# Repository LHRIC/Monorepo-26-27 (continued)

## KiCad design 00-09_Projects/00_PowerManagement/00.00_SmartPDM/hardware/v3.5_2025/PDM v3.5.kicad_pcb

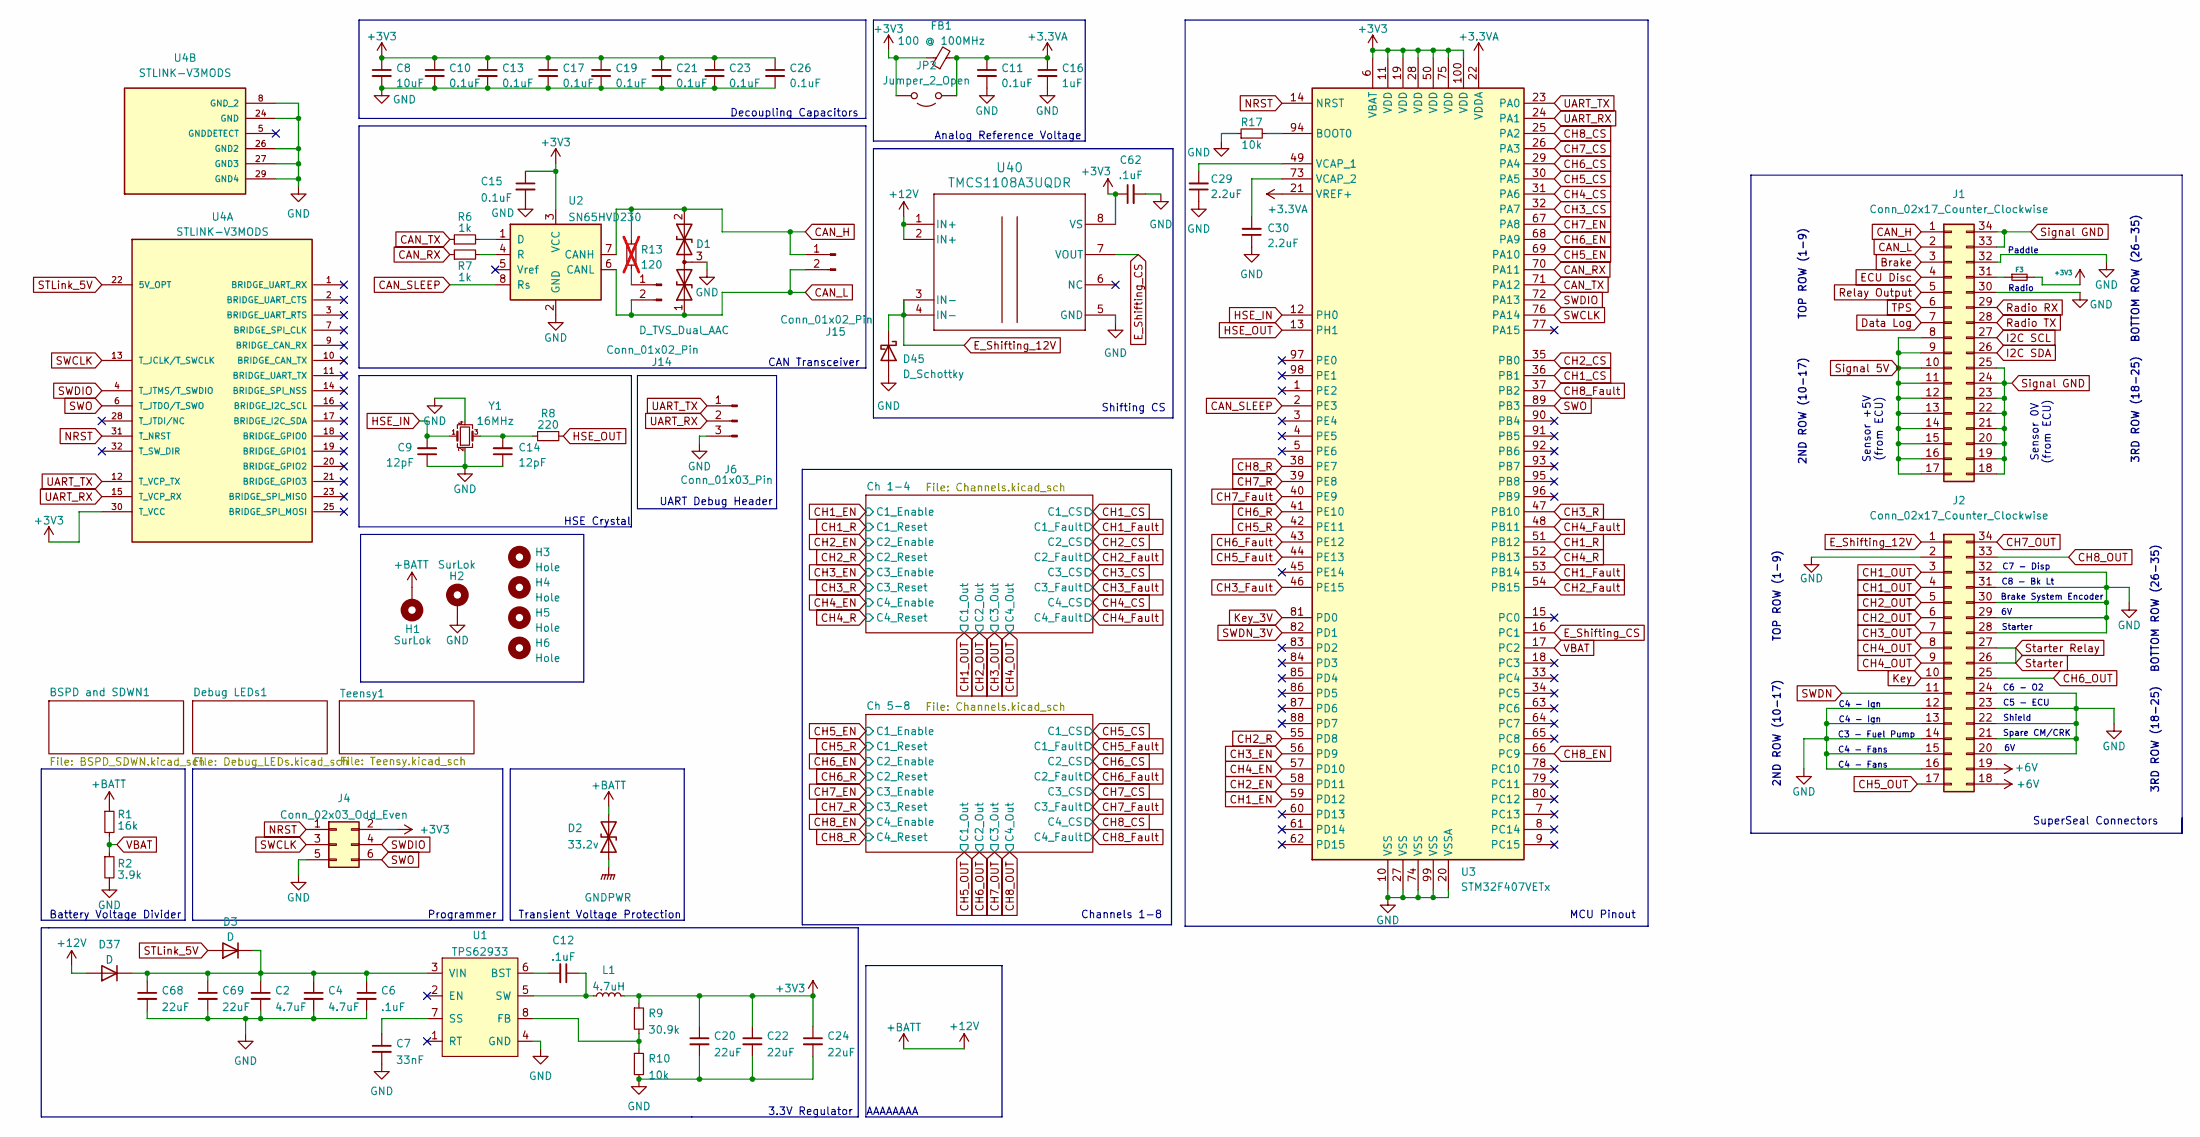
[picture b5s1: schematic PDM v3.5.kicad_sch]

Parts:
C2, C4: 4.7uF; C_0805_2012Metric
C6, C12, C62: .1uF; C_0603_1608Metric
C7: 33nF; C_0603_1608Metric
C8: 10uF; C_0805_2012Metric
C9, C14: 12pF; C_0402_1005Metric
C10, C11, C13, C15, C17, C19, C21, C23, C26: 0.1uF; C_0603_1608Metric
C16: 1uF; C_0603_1608Metric
C20, C22, C24, C68, C69: 22uF; C_0805_2012Metric
C29, C30: 2.2uF; C_0603_1608Metric
D1: D_TVS_Dual_AAC; SOT-23
D2: 33.2v; D_SMB
D3, D37: D; D_PowerDI-123
D45: D_Schottky; D_SOD-523
F3: Fuse_1206_3216Metric; LCSC C70071
FB1: 100 @ 100MHz; C_0402_1005Metric
H1, H2: SurLok; SurLok_5.7
H3, H4, H5, H6: Hole; MountingHole_3.2mm_M3
J1: Conn_02x17_Counter_Clockwise; TE_6437288-1
J2: Conn_02x17_Counter_Clockwise; TE_6437288-2
J4: Conn_02x03_Odd_Even; Molex_Micro-Fit_3.0_43045-0612_2x03_P3.00mm_Vertical
J6: Conn_01x03_Pin; PinHeader_1x03_P2.54mm_Vertical
J14, J15: Conn_01x02_Pin; PinHeader_1x02_P2.54mm_Vertical
JP2: Jumper_2_Open; SolderJumper-2_P1.3mm_Open_RoundedPad1.0x1.5mm
L1: 4.7uH; SRU8043-4R7Y
R1: 16k; R_0603_1608Metric
R2: 3.9k; R_0603_1608Metric
R6, R7: 1k; R_0603_1608Metric
R8: 220; R_0603_1608Metric
R9: 30.9k; R_0603_1608Metric
R10, R17: 10k; R_0603_1608Metric
R13: 120; R_0603_1608Metric; not fitted
U1: TPS62933; SOT-583
U2: SN65HVD230; SOIC-8_3.9x4.9mm_P1.27mm
U3: STM32F407VETx; LQFP-100_14x14mm_P0.5mm
U4: STLINK-V3MODS; MODULE_STLINK-V3MODS; PARTREV 1; DigiKey_Part_Number 497-STLINK-V3MODS-ND
U40: TMCS1108A3UQDR; SOIC-8_3.9x4.9mm_P1.27mm
Y1: 16MHz; Crystal_SMD_3225-4Pin_3.2x2.5mm

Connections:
+3.3VA: C11.1, C16.1, FB1.2, JP2.1 (A), U3.21 (VREF+), U3.22 (VDDA)
+3V3: C8.1, C10.1, C13.1, C15.1, C17.1, C19.1, C20.1, C21.1, C22.1, C23.1, C24.1, C26.1, C62.1, F3.2, FB1.1, J4.2, JP2.2 (B), L1.2, R9.1, U2.3 (VCC), U3.6 (VBAT), U3.11 (VDD), U3.19 (VDD), U3.28 (VDD), U3.50 (VDD), U3.75 (VDD), U3.100 (VDD), U4.30 (T_VCC), U40.8 (VS); also elsewhere on the board
+6V: J2.18, J2.19; also elsewhere on the board
+12V: D2.2 (A2), D37.2 (A), H1.1, R1.1, U40.1 (IN+), U40.2 (IN+); also elsewhere on the board
Brake: J1.3; also elsewhere on the board
CAN_H: D1.2 (A2), J1.1, J15.1, R13.1, U2.7 (CANH); also elsewhere on the board
CAN_L: D1.1 (A1), J1.2, J14.2, J15.2, U2.6 (CANL); also elsewhere on the board
CAN_RX: R7.1, U3.70 (PA11)
CAN_SLEEP: U2.8 (Rs), U3.2 (PE3)
CAN_TX: R6.1, U3.71 (PA12)
CH1_CS: U3.36 (PB1); also elsewhere on the board
CH1_EN: U3.59 (PD12); also elsewhere on the board
CH1_Fault: U3.53 (PB14); also elsewhere on the board
CH1_OUT: J2.3, J2.4; also elsewhere on the board
CH1_R: U3.51 (PB12); also elsewhere on the board
CH2_CS: U3.35 (PB0); also elsewhere on the board
CH2_EN: U3.58 (PD11); also elsewhere on the board
CH2_Fault: U3.54 (PB15); also elsewhere on the board
CH2_OUT: J2.5, J2.6; also elsewhere on the board
CH2_R: U3.55 (PD8); also elsewhere on the board
CH3_CS: U3.32 (PA7); also elsewhere on the board
CH3_EN: U3.56 (PD9); also elsewhere on the board
CH3_Fault: U3.46 (PE15); also elsewhere on the board
CH3_OUT: J2.7; also elsewhere on the board
CH3_R: U3.47 (PB10); also elsewhere on the board
CH4_CS: U3.31 (PA6); also elsewhere on the board
CH4_EN: U3.57 (PD10); also elsewhere on the board
CH4_Fault: U3.48 (PB11); also elsewhere on the board
CH4_OUT: J2.8, J2.9; also elsewhere on the board
CH4_R: U3.52 (PB13); also elsewhere on the board
CH5_CS: U3.30 (PA5); also elsewhere on the board
CH5_EN: U3.69 (PA10); also elsewhere on the board
CH5_Fault: U3.44 (PE13); also elsewhere on the board
CH5_OUT: J2.17; also elsewhere on the board
CH5_R: U3.42 (PE11); also elsewhere on the board
CH6_CS: U3.29 (PA4); also elsewhere on the board
CH6_EN: U3.68 (PA9); also elsewhere on the board
CH6_Fault: U3.43 (PE12); also elsewhere on the board
CH6_OUT: J2.25; also elsewhere on the board
CH6_R: U3.41 (PE10); also elsewhere on the board
CH7_CS: U3.26 (PA3); also elsewhere on the board
CH7_EN: U3.67 (PA8); also elsewhere on the board
CH7_Fault: U3.40 (PE9); also elsewhere on the board
CH7_OUT: J2.34; also elsewhere on the board
CH7_R: U3.39 (PE8); also elsewhere on the board
CH8_CS: U3.25 (PA2); also elsewhere on the board
CH8_EN: U3.66 (PC9); also elsewhere on the board
CH8_Fault: U3.37 (PB2); also elsewhere on the board
CH8_OUT: J2.33; also elsewhere on the board
CH8_R: U3.38 (PE7); also elsewhere on the board
Data Log: J1.7; also elsewhere on the board
ECU Disc: J1.4; also elsewhere on the board
E_Shifting_12V: D45.1 (K), J2.1, U40.3 (IN-), U40.4 (IN-)
E_Shifting_CS: U3.16 (PC1), U40.7 (VOUT)
GND: C2.2, C4.2, C6.2, C7.2, C8.2, C9.1, C10.2, C11.2, C13.2, C14.1, C15.2, C16.2, C17.2, C19.2, C20.2, C21.2, C22.2, C23.2, C24.2, C26.2, C29.1, C30.1, C62.2, C68.2, C69.2, D1.3 (common), D45.2 (A), H2.1, J1.30, J1.32, J2.2, J2.12, J2.13, J2.14, J2.15, J2.16, J2.20, J2.21, J2.22, J2.23, J2.24, J2.28, J2.29, J2.30, J2.31, J2.32, J4.5, J6.3, R2.2, R10.2, R17.1, U1.4 (GND), U2.2 (GND), U3.10 (VSS), U3.20 (VSSA), U3.27 (VSS), U3.74 (VSS), U3.99 (VSS), U4.8 (GND_2), U4.24 (GND), U4.26 (GND2), U4.27 (GND3), U4.29 (GND4), U40.5 (GND), Y1.2, Y1.4; also elsewhere on the board
GNDPWR: D2.1 (A1)
HSE_IN: C9.2, U3.12 (PH0), Y1.1
HSE_OUT: R8.2, U3.13 (PH1)
I2C SCL: J1.27; also elsewhere on the board
I2C SDA: J1.26; also elsewhere on the board
Key: J2.10; also elsewhere on the board
Key_3V: U3.81 (PD0); also elsewhere on the board
NRST: J4.1, U3.14 (NRST), U4.31 (T_NRST)
unnamed: C14.2, R8.1, Y1.3
unnamed: C2.1, C4.1, C6.1, C68.1, C69.1, D3.1 (K), D37.1 (K), U1.3 (VIN)
unnamed: F3.1, J1.31
unnamed: J14.1, R13.2
unnamed: C12.2, U1.6 (BST)
unnamed: R9.2, R10.1, U1.8 (FB)
unnamed: C7.1, U1.7 (SS)
unnamed: C12.1, L1.1, U1.5 (SW)
unnamed: R6.2, U2.1 (D)
unnamed: R7.2, U2.4 (R)
unnamed: R17.2, U3.94 (BOOT0)
unnamed: C29.2, U3.49 (VCAP_1)
unnamed: C30.2, U3.73 (VCAP_2)
Radio RX: J1.29; also elsewhere on the board
Radio TX: J1.28; also elsewhere on the board
Relay Output: J1.5; also elsewhere on the board
STLink_5V: D3.2 (A), U4.22 (5V_OPT)
SWCLK: J4.3, U3.76 (PA14), U4.13 (T_JCLK/T_SWCLK)
SWDIO: J4.4, U3.72 (PA13), U4.4 (T_JTMS/T_SWDIO)
SWDN: J2.11; also elsewhere on the board
SWDN_3V: U3.82 (PD1); also elsewhere on the board
SWO: J4.6, U3.89 (PB3), U4.6 (T_JTDO/T_SWO)
Signal 5V: J1.8, J1.9, J1.10, J1.11, J1.12, J1.13, J1.14, J1.15, J1.16, J1.17
Signal GND: J1.18, J1.19, J1.20, J1.21, J1.22, J1.23, J1.24, J1.25, J1.33, J1.34
Starter: J2.26, J2.27
TPS: J1.6; also elsewhere on the board
UART_RX: J6.2, U3.24 (PA1), U4.15 (T_VCP_RX)
UART_TX: J6.1, U3.23 (PA0), U4.12 (T_VCP_TX)
VBAT: R1.2, R2.1, U3.17 (PC2)

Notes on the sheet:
C3 - Fuel Pump
Starter
TOP ROW (1-9)
Spare CM/CRK
3RD ROW (18-25)
Brake System Encoder
BOTTOM ROW (26-35)
MCU Pinout
UART Debug Header
2ND ROW (10-17)
C4 - Fans
Transient Voltage Protection
SuperSeal Connectors
HSE Crystal
Paddle
C5 - ECU
Radio
Shield
C6 - O2
3.3V Regulator
C4 - Ign
C7 - Disp
C8 - Bk Lt
Sensor +5V (from ECU)
Channels 1-8
Decoupling Capacitors
Battery Voltage Divider
CAN Transceiver
AAAAAAAA
Shifting CS
Programmer
Sensor 0V (from ECU)
Analog Reference Voltage

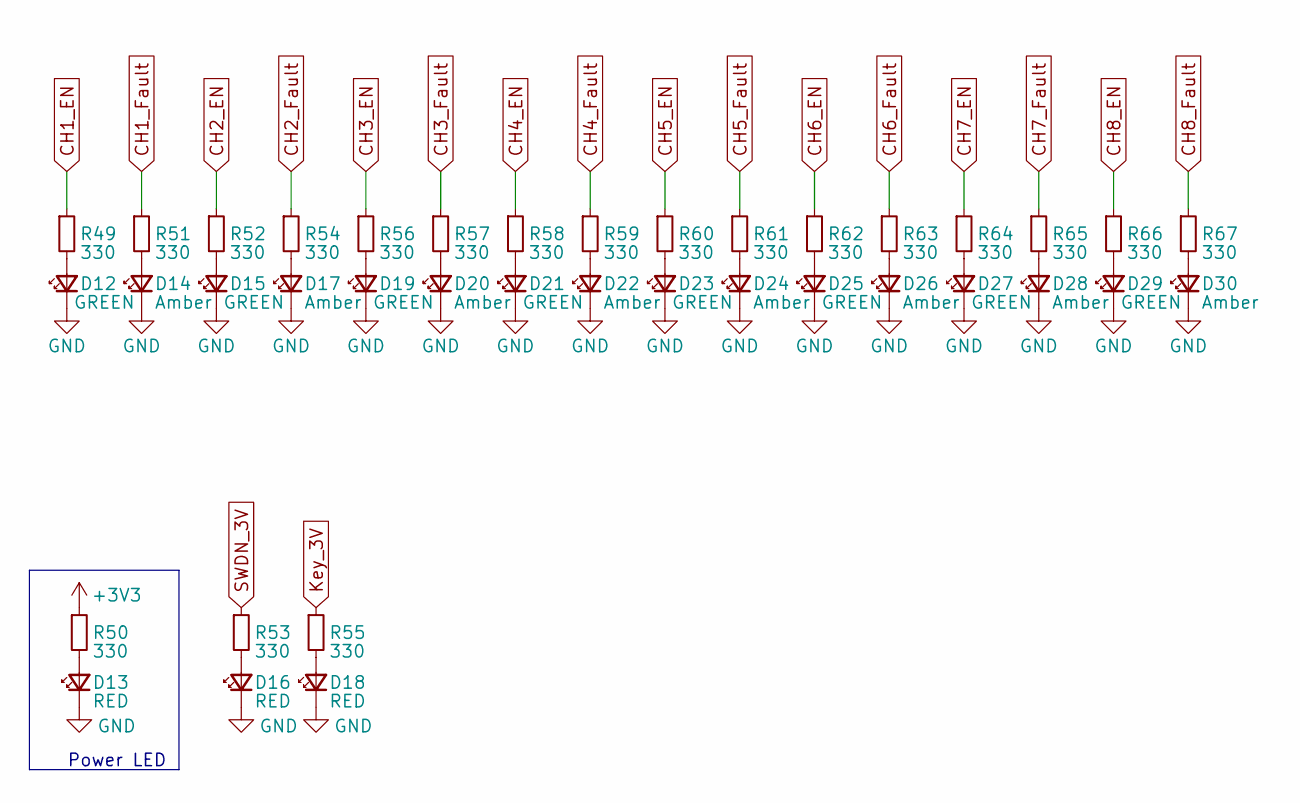
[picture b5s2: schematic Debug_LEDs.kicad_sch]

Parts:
D12, D15, D19, D21, D23, D25, D27, D29: GREEN; LED_0603_1608Metric
D13, D16, D18: RED; LED_0603_1608Metric
D14, D17, D20, D22, D24, D26, D28, D30: Amber; LED_0603_1608Metric
R49, R50, R51, R52, R53, R54, R55, R56, R57, R58, R59, R60, R61, R62, R63, R64, R65, R66, R67: 330; R_0603_1608Metric

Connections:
+3V3: R50.1; also elsewhere on the board
CH1_EN: R49.1; also elsewhere on the board
CH1_Fault: R51.1; also elsewhere on the board
CH2_EN: R52.1; also elsewhere on the board
CH2_Fault: R54.1; also elsewhere on the board
CH3_EN: R56.1; also elsewhere on the board
CH3_Fault: R57.1; also elsewhere on the board
CH4_EN: R58.1; also elsewhere on the board
CH4_Fault: R59.1; also elsewhere on the board
CH5_EN: R60.1; also elsewhere on the board
CH5_Fault: R61.1; also elsewhere on the board
CH6_EN: R62.1; also elsewhere on the board
CH6_Fault: R63.1; also elsewhere on the board
CH7_EN: R64.1; also elsewhere on the board
CH7_Fault: R65.1; also elsewhere on the board
CH8_EN: R66.1; also elsewhere on the board
CH8_Fault: R67.1; also elsewhere on the board
GND: D12.1 (K), D13.1 (K), D14.1 (K), D15.1 (K), D16.1 (K), D17.1 (K), D18.1 (K), D19.1 (K), D20.1 (K), D21.1 (K), D22.1 (K), D23.1 (K), D24.1 (K), D25.1 (K), D26.1 (K), D27.1 (K), D28.1 (K), D29.1 (K), D30.1 (K); also elsewhere on the board
Key_3V: R55.1; also elsewhere on the board
unnamed: D12.2 (A), R49.2
unnamed: D13.2 (A), R50.2
unnamed: D14.2 (A), R51.2
unnamed: D15.2 (A), R52.2
unnamed: D16.2 (A), R53.2
unnamed: D17.2 (A), R54.2
unnamed: D18.2 (A), R55.2
unnamed: D19.2 (A), R56.2
unnamed: D20.2 (A), R57.2
unnamed: D21.2 (A), R58.2
unnamed: D22.2 (A), R59.2
unnamed: D23.2 (A), R60.2
unnamed: D24.2 (A), R61.2
unnamed: D25.2 (A), R62.2
unnamed: D26.2 (A), R63.2
unnamed: D27.2 (A), R64.2
unnamed: D28.2 (A), R65.2
unnamed: D29.2 (A), R66.2
unnamed: D30.2 (A), R67.2
SWDN_3V: R53.1; also elsewhere on the board

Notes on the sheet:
Power LED

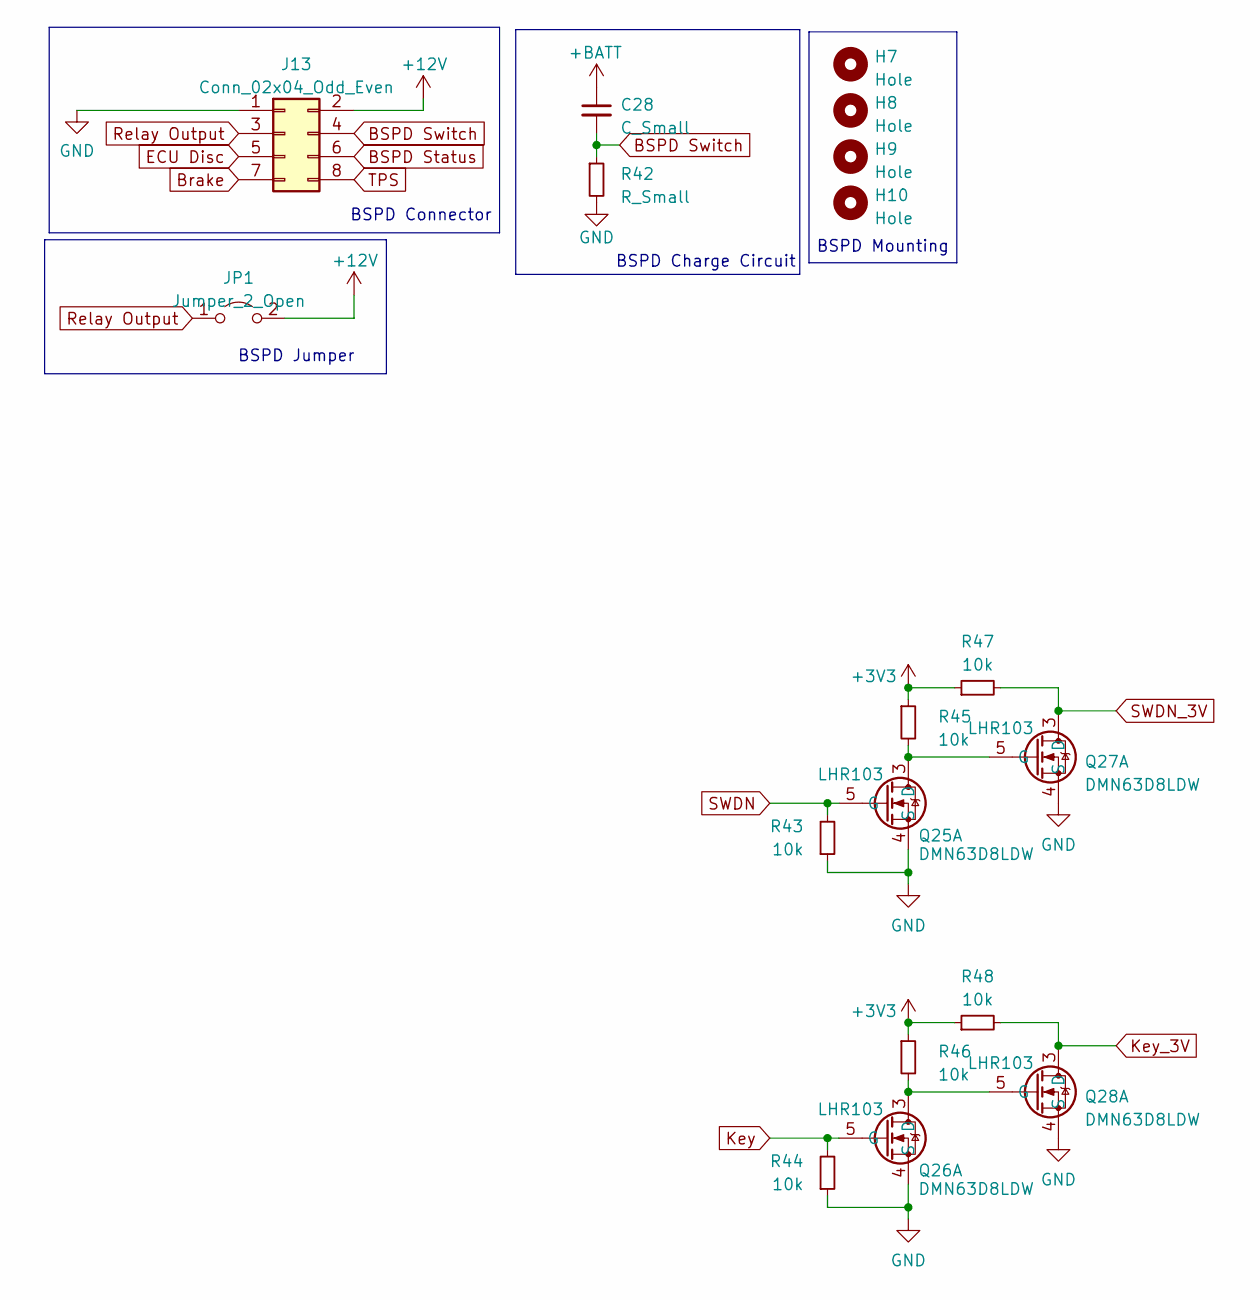
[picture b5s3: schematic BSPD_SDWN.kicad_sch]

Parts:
C28: C_Small; C_0805_2012Metric
H7, H8, H9, H10: Hole; MountingHole_3.7mm
J13: Conn_02x04_Odd_Even; SAMTEC-SFM-104-02-X-D-A
JP1: Jumper_2_Open; SolderJumper-2_P1.3mm_Open_RoundedPad1.0x1.5mm
Q25, Q26, Q27, Q28: DMN63D8LDW; SOT-363_SC-70-6
R42: R_Small; R_0603_1608Metric
R43, R44, R45, R46, R47, R48: 10k; R_0603_1608Metric

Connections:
+3V3: R45.1, R46.1, R47.1, R48.1; also elsewhere on the board
+12V: C28.1, J13.2, JP1.2 (B); also elsewhere on the board
BSPD Status: J13.6; also elsewhere on the board
BSPD Switch: C28.2, J13.4, R42.1
Brake: J13.7; also elsewhere on the board
ECU Disc: J13.5; also elsewhere on the board
GND: J13.1, Q25.4 (S), Q26.4 (S), Q27.4 (S), Q28.4 (S), R42.2, R43.1, R44.1; also elsewhere on the board
Key: Q26.5 (G), R44.2; also elsewhere on the board
Key_3V: Q28.3 (D), R48.2; also elsewhere on the board
unnamed: Q25.3 (D), Q27.5 (G), R45.2
unnamed: Q26.3 (D), Q28.5 (G), R46.2
Relay Output: J13.3, JP1.1 (A); also elsewhere on the board
SWDN: Q25.5 (G), R43.2; also elsewhere on the board
SWDN_3V: Q27.3 (D), R47.2; also elsewhere on the board
TPS: J13.8; also elsewhere on the board

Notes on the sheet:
BSPD Charge Circuit
BSPD Mounting
BSPD Connector
BSPD Jumper

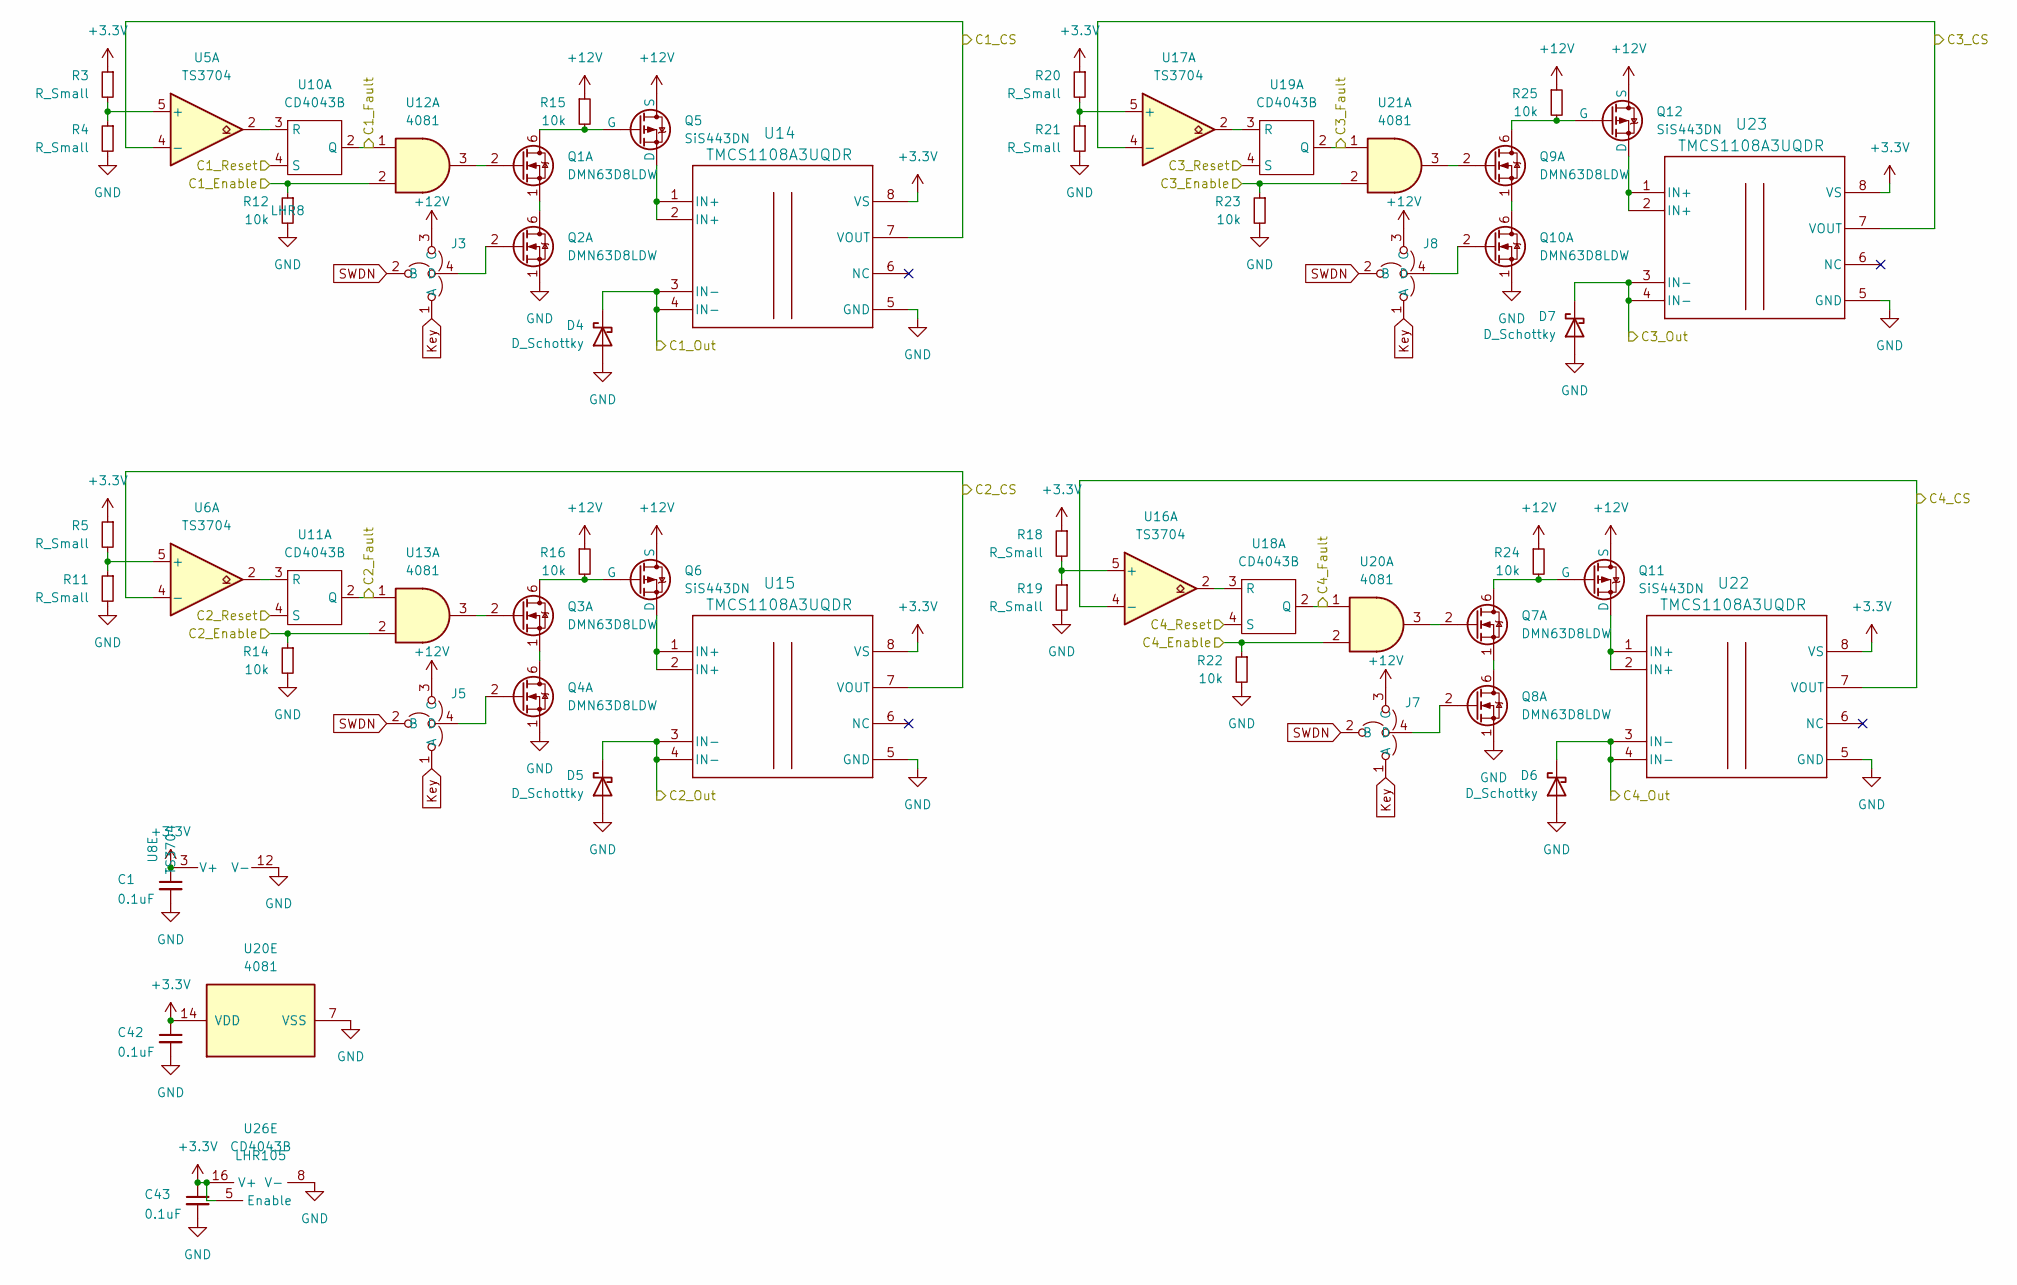
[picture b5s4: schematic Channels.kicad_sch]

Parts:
C1, C42, C43: 0.1uF; C_0603_1608Metric
D4, D5, D6, D7: D_Schottky; D_SOD-523
J3, J5, J7, J8: SolderJumper-4_P1.3mm_Open_Rounded
Q1, Q2, Q3, Q4, Q7, Q8, Q9, Q10: DMN63D8LDW; SOT-363_SC-70-6
Q5, Q6, Q11, Q12: SiS443DN; Vishay_PowerPAK_1212-8_Single
R3, R4, R5, R11, R18, R19, R20, R21: R_Small; R_0603_1608Metric
R12, R14, R15, R16, R22, R23, R24, R25: 10k; R_0603_1608Metric
U5, U6, U8, U16, U17: TS3704; TSSOP-14_4.4x5mm_P0.65mm
U10, U11, U18, U19, U26: CD4043B; SOIC-16_3.9x9.9mm_P1.27mm
U12, U13, U20, U21: 4081; TSSOP-14_4.4x5mm_P0.65mm
U14, U15, U22, U23: TMCS1108A3UQDR; SOIC-8_3.9x4.9mm_P1.27mm

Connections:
+3.3V: C1.1, C42.1, C43.1, R3.1, R5.1, R18.1, R20.1, U8.3 (V+), U14.8 (VS), U15.8 (VS), U20.14 (VDD), U21.14 (VDD), U22.8 (VS), U23.8 (VS), U26.5 (Enable), U26.16 (V+); also elsewhere on the board
+12V: J3.3 (C), J5.3 (C), J7.3 (C), J8.3 (C), Q5.1 (S), Q5.2 (S), Q5.3 (S), Q6.1 (S), Q6.2 (S), Q6.3 (S), Q11.1 (S), Q11.2 (S), Q11.3 (S), Q12.1 (S), Q12.2 (S), Q12.3 (S), R15.1, R16.1, R24.1, R25.1; also elsewhere on the board
CH1_CS: U5.4 (-), U14.7 (VOUT); also elsewhere on the board
CH1_EN: R12.1, U12.2; also elsewhere on the board
CH1_Fault: U10.2 (Q), U12.1; also elsewhere on the board
CH1_OUT: D4.1 (K), U14.3 (IN-), U14.4 (IN-); also elsewhere on the board
CH1_R: U10.4 (S); also elsewhere on the board
CH2_CS: U6.4 (-), U15.7 (VOUT); also elsewhere on the board
CH2_EN: R14.1, U13.2; also elsewhere on the board
CH2_Fault: U11.2 (Q), U13.1; also elsewhere on the board
CH2_OUT: D5.1 (K), U15.3 (IN-), U15.4 (IN-); also elsewhere on the board
CH2_R: U11.4 (S); also elsewhere on the board
CH3_CS: U17.4 (-), U23.7 (VOUT); also elsewhere on the board
CH3_EN: R23.1, U21.2; also elsewhere on the board
CH3_Fault: U19.2 (Q), U21.1; also elsewhere on the board
CH3_OUT: D7.1 (K), U23.3 (IN-), U23.4 (IN-); also elsewhere on the board
CH3_R: U19.4 (S); also elsewhere on the board
CH4_CS: U16.4 (-), U22.7 (VOUT); also elsewhere on the board
CH4_EN: R22.1, U20.2; also elsewhere on the board
CH4_Fault: U18.2 (Q), U20.1; also elsewhere on the board
CH4_OUT: D6.1 (K), U22.3 (IN-), U22.4 (IN-); also elsewhere on the board
CH4_R: U18.4 (S); also elsewhere on the board
GND: C1.2, C42.2, C43.2, D4.2 (A), D5.2 (A), D6.2 (A), D7.2 (A), Q2.1 (S), Q4.1 (S), Q8.1 (S), Q10.1 (S), R4.2, R11.2, R12.2, R14.2, R19.2, R21.2, R22.2, R23.2, U8.12 (V-), U14.5 (GND), U15.5 (GND), U20.7 (VSS), U21.7 (VSS), U22.5 (GND), U23.5 (GND), U26.8 (V-); also elsewhere on the board
Key: J3.1 (A), J5.1 (A), J7.1 (A), J8.1 (A); also elsewhere on the board
unnamed: J3.4 (D), Q2.2 (G)
unnamed: J5.4 (D), Q4.2 (G)
unnamed: J7.4 (D), Q8.2 (G)
unnamed: J8.4 (D), Q10.2 (G)
unnamed: Q1.6 (D), Q5.4 (G), R15.2
unnamed: Q1.2 (G), U12.3
unnamed: Q1.1 (S), Q2.6 (D)
unnamed: Q3.6 (D), Q6.4 (G), R16.2
unnamed: Q3.2 (G), U13.3
unnamed: Q3.1 (S), Q4.6 (D)
unnamed: Q5.5 (D), U14.1 (IN+), U14.2 (IN+)
unnamed: Q6.5 (D), U15.1 (IN+), U15.2 (IN+)
unnamed: Q7.2 (G), U20.3
unnamed: Q7.1 (S), Q8.6 (D)
unnamed: Q9.2 (G), U21.3
unnamed: Q9.1 (S), Q10.6 (D)
unnamed: Q11.5 (D), U22.1 (IN+), U22.2 (IN+)
unnamed: Q7.6 (D), Q11.4 (G), R24.2
unnamed: Q12.5 (D), U23.1 (IN+), U23.2 (IN+)
unnamed: Q9.6 (D), Q12.4 (G), R25.2
unnamed: R3.2, R4.1, U5.5 (+)
unnamed: R5.2, R11.1, U6.5 (+)
unnamed: U5.2, U10.3 (R)
unnamed: U6.2, U11.3 (R)
unnamed: R18.2, R19.1, U16.5 (+)
unnamed: R20.2, R21.1, U17.5 (+)
unnamed: U16.2, U18.3 (R)
unnamed: U17.2, U19.3 (R)
SWDN: J3.2 (B), J5.2 (B), J7.2 (B), J8.2 (B); also elsewhere on the board

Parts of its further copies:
C3, C44, C45: 0.1uF; C_0603_1608Metric
D8, D9, D10, D11: D_Schottky; D_SOD-523
J9, J10, J11, J12: SolderJumper-4_P1.3mm_Open_Rounded
Q13, Q14, Q15, Q16, Q19, Q20, Q21, Q22: DMN63D8LDW; SOT-363_SC-70-6
Q17, Q18, Q23, Q24: SiS443DN; Vishay_PowerPAK_1212-8_Single
R26, R27, R28, R29, R34, R35, R36, R37: R_Small; R_0603_1608Metric
R30, R31, R32, R33, R38, R39, R40, R41: 10k; R_0603_1608Metric
U9, U24, U25, U35, U36: TS3704; TSSOP-14_4.4x5mm_P0.65mm
U27, U29, U30, U37, U38: CD4043B; SOIC-16_3.9x9.9mm_P1.27mm
U31, U32, U39, U41: 4081; TSSOP-14_4.4x5mm_P0.65mm
U33, U34, U42, U43: TMCS1108A3UQDR; SOIC-8_3.9x4.9mm_P1.27mm

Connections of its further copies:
+3.3V: C3.1, C44.1, C45.1, R26.1, R28.1, R34.1, R36.1, U9.3 (V+), U27.5 (Enable), U27.16 (V+), U33.8 (VS), U34.8 (VS), U42.8 (VS), U43.8 (VS); also elsewhere on the board
+12V: J9.3 (C), J10.3 (C), J11.3 (C), J12.3 (C), Q17.1 (S), Q17.2 (S), Q17.3 (S), Q18.1 (S), Q18.2 (S), Q18.3 (S), Q23.1 (S), Q23.2 (S), Q23.3 (S), Q24.1 (S), Q24.2 (S), Q24.3 (S), R32.1, R33.1, R40.1, R41.1; also elsewhere on the board
CH5_CS: U24.4 (-), U33.7 (VOUT); also elsewhere on the board
CH5_EN: R30.1, U31.2; also elsewhere on the board
CH5_Fault: U29.2 (Q), U31.1; also elsewhere on the board
CH5_OUT: D8.1 (K), U33.3 (IN-), U33.4 (IN-); also elsewhere on the board
CH5_R: U29.4 (S); also elsewhere on the board
CH6_CS: U25.4 (-), U34.7 (VOUT); also elsewhere on the board
CH6_EN: R31.1, U32.2; also elsewhere on the board
CH6_Fault: U30.2 (Q), U32.1; also elsewhere on the board
CH6_OUT: D9.1 (K), U34.3 (IN-), U34.4 (IN-); also elsewhere on the board
CH6_R: U30.4 (S); also elsewhere on the board
CH7_CS: U36.4 (-), U43.7 (VOUT); also elsewhere on the board
CH7_EN: R39.1, U41.2; also elsewhere on the board
CH7_Fault: U38.2 (Q), U41.1; also elsewhere on the board
CH7_OUT: D11.1 (K), U43.3 (IN-), U43.4 (IN-); also elsewhere on the board
CH7_R: U38.4 (S); also elsewhere on the board
CH8_CS: U35.4 (-), U42.7 (VOUT); also elsewhere on the board
CH8_EN: R38.1, U39.2; also elsewhere on the board
CH8_Fault: U37.2 (Q), U39.1; also elsewhere on the board
CH8_OUT: D10.1 (K), U42.3 (IN-), U42.4 (IN-); also elsewhere on the board
CH8_R: U37.4 (S); also elsewhere on the board
GND: C3.2, C44.2, C45.2, D8.2 (A), D9.2 (A), D10.2 (A), D11.2 (A), Q14.1 (S), Q16.1 (S), Q20.1 (S), Q22.1 (S), R27.2, R29.2, R30.2, R31.2, R35.2, R37.2, R38.2, R39.2, U9.12 (V-), U27.8 (V-), U33.5 (GND), U34.5 (GND), U42.5 (GND), U43.5 (GND); also elsewhere on the board
Key: J9.1 (A), J10.1 (A), J11.1 (A), J12.1 (A); also elsewhere on the board
unnamed: J9.4 (D), Q14.2 (G)
unnamed: J10.4 (D), Q16.2 (G)
unnamed: J11.4 (D), Q20.2 (G)
unnamed: J12.4 (D), Q22.2 (G)
unnamed: Q13.6 (D), Q17.4 (G), R32.2
unnamed: Q13.2 (G), U31.3
unnamed: Q13.1 (S), Q14.6 (D)
unnamed: Q15.6 (D), Q18.4 (G), R33.2
unnamed: Q15.2 (G), U32.3
unnamed: Q15.1 (S), Q16.6 (D)
unnamed: Q17.5 (D), U33.1 (IN+), U33.2 (IN+)
unnamed: Q18.5 (D), U34.1 (IN+), U34.2 (IN+)
unnamed: Q19.6 (D), Q23.4 (G), R40.2
unnamed: Q19.2 (G), U39.3
unnamed: Q19.1 (S), Q20.6 (D)
unnamed: Q21.6 (D), Q24.4 (G), R41.2
unnamed: Q21.2 (G), U41.3
unnamed: Q21.1 (S), Q22.6 (D)
unnamed: Q23.5 (D), U42.1 (IN+), U42.2 (IN+)
unnamed: Q24.5 (D), U43.1 (IN+), U43.2 (IN+)
unnamed: R26.2, R27.1, U24.5 (+)
unnamed: R28.2, R29.1, U25.5 (+)
unnamed: U24.2, U29.3 (R)
unnamed: U25.2, U30.3 (R)
unnamed: R34.2, R35.1, U35.5 (+)
unnamed: R36.2, R37.1, U36.5 (+)
unnamed: U35.2, U37.3 (R)
unnamed: U36.2, U38.3 (R)
SWDN: J9.2 (B), J10.2 (B), J11.2 (B), J12.2 (B); also elsewhere on the board

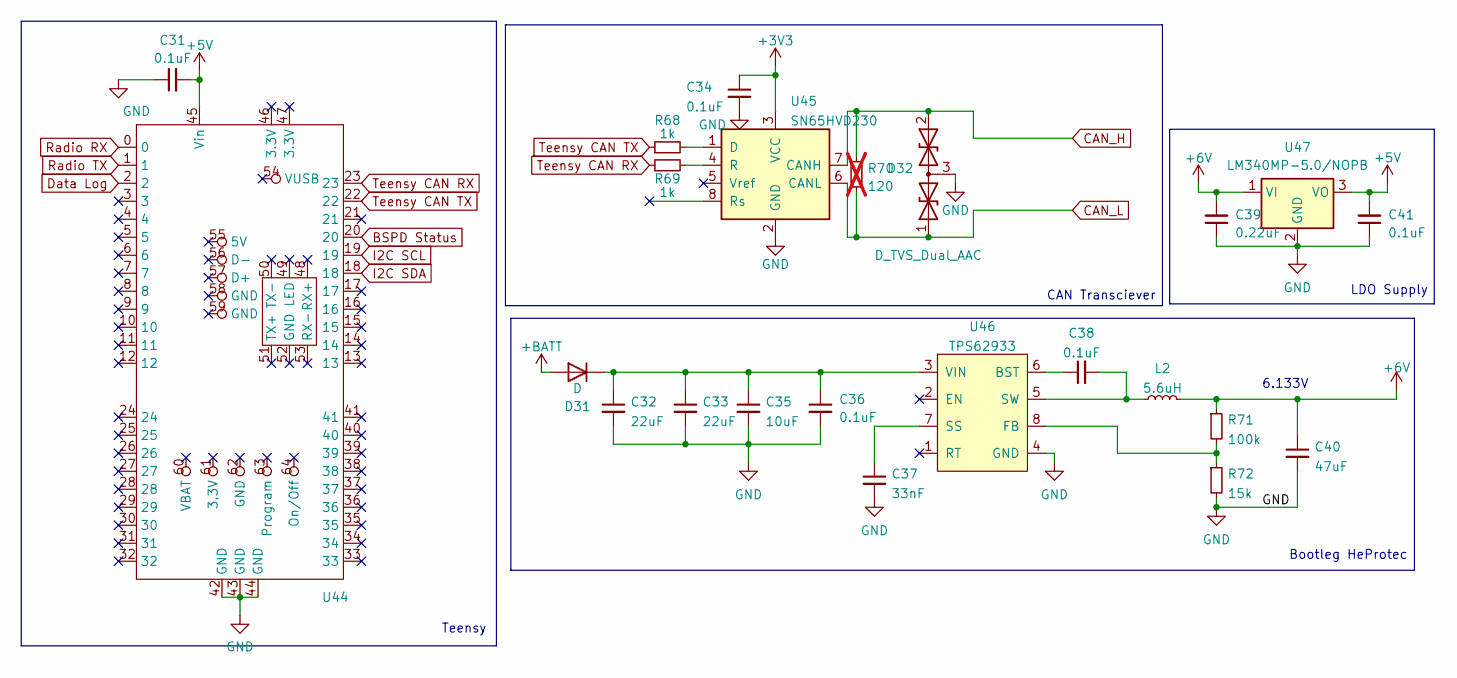
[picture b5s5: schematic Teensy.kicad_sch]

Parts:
C31, C34, C36, C38, C41: 0.1uF; C_0603_1608Metric
C32, C33: 22uF; C_0805_2012Metric
C35: 10uF; C_0805_2012Metric
C37: 33nF; C_0603_1608Metric
C39: 0.22uF; C_0603_1608Metric
C40: 47uF; C_0603_1608Metric
D31: D; D_PowerDI-123
D32: D_TVS_Dual_AAC; SOT-23
L2: 5.6uH; HCMA1305-5R6-R
R68, R69: 1k; R_0603_1608Metric
R70: 120; R_0603_1608Metric; not fitted
R71: 100k; R_0603_1608Metric
R72: 15k; R_0603_1608Metric
U44: Teensy 4.1
U45: SN65HVD230; SOIC-8_3.9x4.9mm_P1.27mm
U46: TPS62933; SOT-583
U47: LM340MP-5.0/NOPB; SOT-223-3_TabPin2

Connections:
+3V3: C34.1, U45.3 (VCC); also elsewhere on the board
+5V: C31.2, C41.2, U44.45 (Vin), U47.3 (VO)
+6V: C39.2, C40.1, L2.2, R71.1, U47.1 (VI); also elsewhere on the board
+12V: D31.2 (A); also elsewhere on the board
BSPD Status: U44.20; also elsewhere on the board
CAN_H: D32.2 (A2), R70.1, U45.7 (CANH); also elsewhere on the board
CAN_L: D32.1 (A1), R70.2, U45.6 (CANL); also elsewhere on the board
Data Log: U44.2; also elsewhere on the board
GND: C31.1, C32.2, C33.2, C34.2, C35.2, C36.2, C37.2, C39.1, C40.2, C41.1, D32.3 (common), R72.2, U44.42 (GND), U44.43 (GND), U44.44 (GND), U45.2 (GND), U46.4 (GND), U47.2 (GND); also elsewhere on the board
I2C SCL: U44.19; also elsewhere on the board
I2C SDA: U44.18; also elsewhere on the board
unnamed: C32.1, C33.1, C35.1, C36.1, D31.1 (K), U46.3 (VIN)
unnamed: R68.2, U45.1 (D)
unnamed: R69.2, U45.4 (R)
unnamed: C38.1, U46.6 (BST)
unnamed: R71.2, R72.1, U46.8 (FB)
unnamed: C37.1, U46.7 (SS)
unnamed: C38.2, L2.1, U46.5 (SW)
Radio RX: U44.0; also elsewhere on the board
Radio TX: U44.1; also elsewhere on the board
Teensy CAN RX: R69.1, U44.23
Teensy CAN TX: R68.1, U44.22

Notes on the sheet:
Bootleg HeProtec
LDO Supply
Teensy
6.133V
CAN Transciever
